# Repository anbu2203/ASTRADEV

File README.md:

## AstraDev
- AstraDev is a custom-designed development board created for embedded systems learning, prototyping, and real-world hardware design experience. The project follows a complete professional workflow—from schematic design to PCB layout, 3D verification, and manufacturing preparation.

# Project Overview
- AstraDev was designed to demonstrate a full PCB development lifecycle using industry-standard practices. The board design emphasizes clean schematics, organized PCB routing, proper grounding, and manufacturing readiness. All files have been verified and prepared for fabrication and assembly through JLCPCB.

# Schematic Design
- The schematic was designed using KiCad Schematic Editor
- All functional blocks were clearly separated:
Power supply and regulation
Microcontroller and clock circuitry
USB interface
Programming/debug interface
GPIO and peripheral connections
CUSTOM DEVBOARD guide-recommended components such as decoupling capacitors, pull-up/down resistors, and protection elements were included
Net labels and reference designators were standardized for clarity
Electrical Rule Check (ERC) was performed to ensure there were no schematic errors
The schematic was finalized and locked before PCB layout
.png)
# PCB Layout and Wiring

- PCB layout was completed using KiCad PCB Editor
- A 2-layer PCB was used:
Top layer (F.Cu) for signal routing
Bottom layer (B.Cu) primarily for ground plane and routing
Components were placed using functional grouping to reduce track length and noise
Power tracks were routed first, followed by critical signals and GPIO lines
Track widths were selected based on signal type:
GPIO and signal lines: minimum safe width
Power lines: wider tracks
A GND copper pour was added on both layers for proper grounding
Thermal reliefs and clearances were adjusted to ensure good solderability
Via stitching was used where necessary to improve ground connectivity
Design Rule Check (DRC) was run and all errors were resolved before production
.png)

# 3D Viewer Verification

- KiCad’s 3D Viewer was used to visually inspect the PCB
Component orientation, alignment, and placement were verified
Mechanical fit of connectors (USB, headers) was checked
Potential assembly issues were identified early
This step ensured the PCB would be physically correct before manufacturing

-  Manufacturing File Preparation:
Gerber and drill files were generated from KiCad
files were verified using Gerber viewer tools
A Bill of Materials (BOM) was generated and modified to meet JLCPCB requirements
A Component Placement List (CPL / Pick-and-Place) file was generated from the PCB editor
BOM and CPL headers were renamed to match JLCPCB’s accepted format
Only top-side assembly files were included
All production files were organized into a single production folder and compressed into a ZIP archive
.png)
.png)

# JLCPCB Checking and PCBA Preparation

- The production ZIP was uploaded to JLCPCB
PCB Assembly (PCBA) option was enabled
ENIG surface finish was selected for reliable soldering and flat pads
BOM components were reviewed:
Missing or incorrect parts were manually reassigned
Basic parts were prioritized to reduce cost
Pin headers and non-essential components were excluded from assembly
Component orientation and placement were verified using JLCPCB’s online PCBA viewer
Final checks were completed before submission
.png)

# Production Status

- Schematic completed and verified

- PCB layout completed and DRC cleared

- 3D verification completed

- BOM and CPL prepared and validated

- Ready for JLCPCB fabrication and assembly

- Awaiting funding for order placement

# Designed and documented by ANBU

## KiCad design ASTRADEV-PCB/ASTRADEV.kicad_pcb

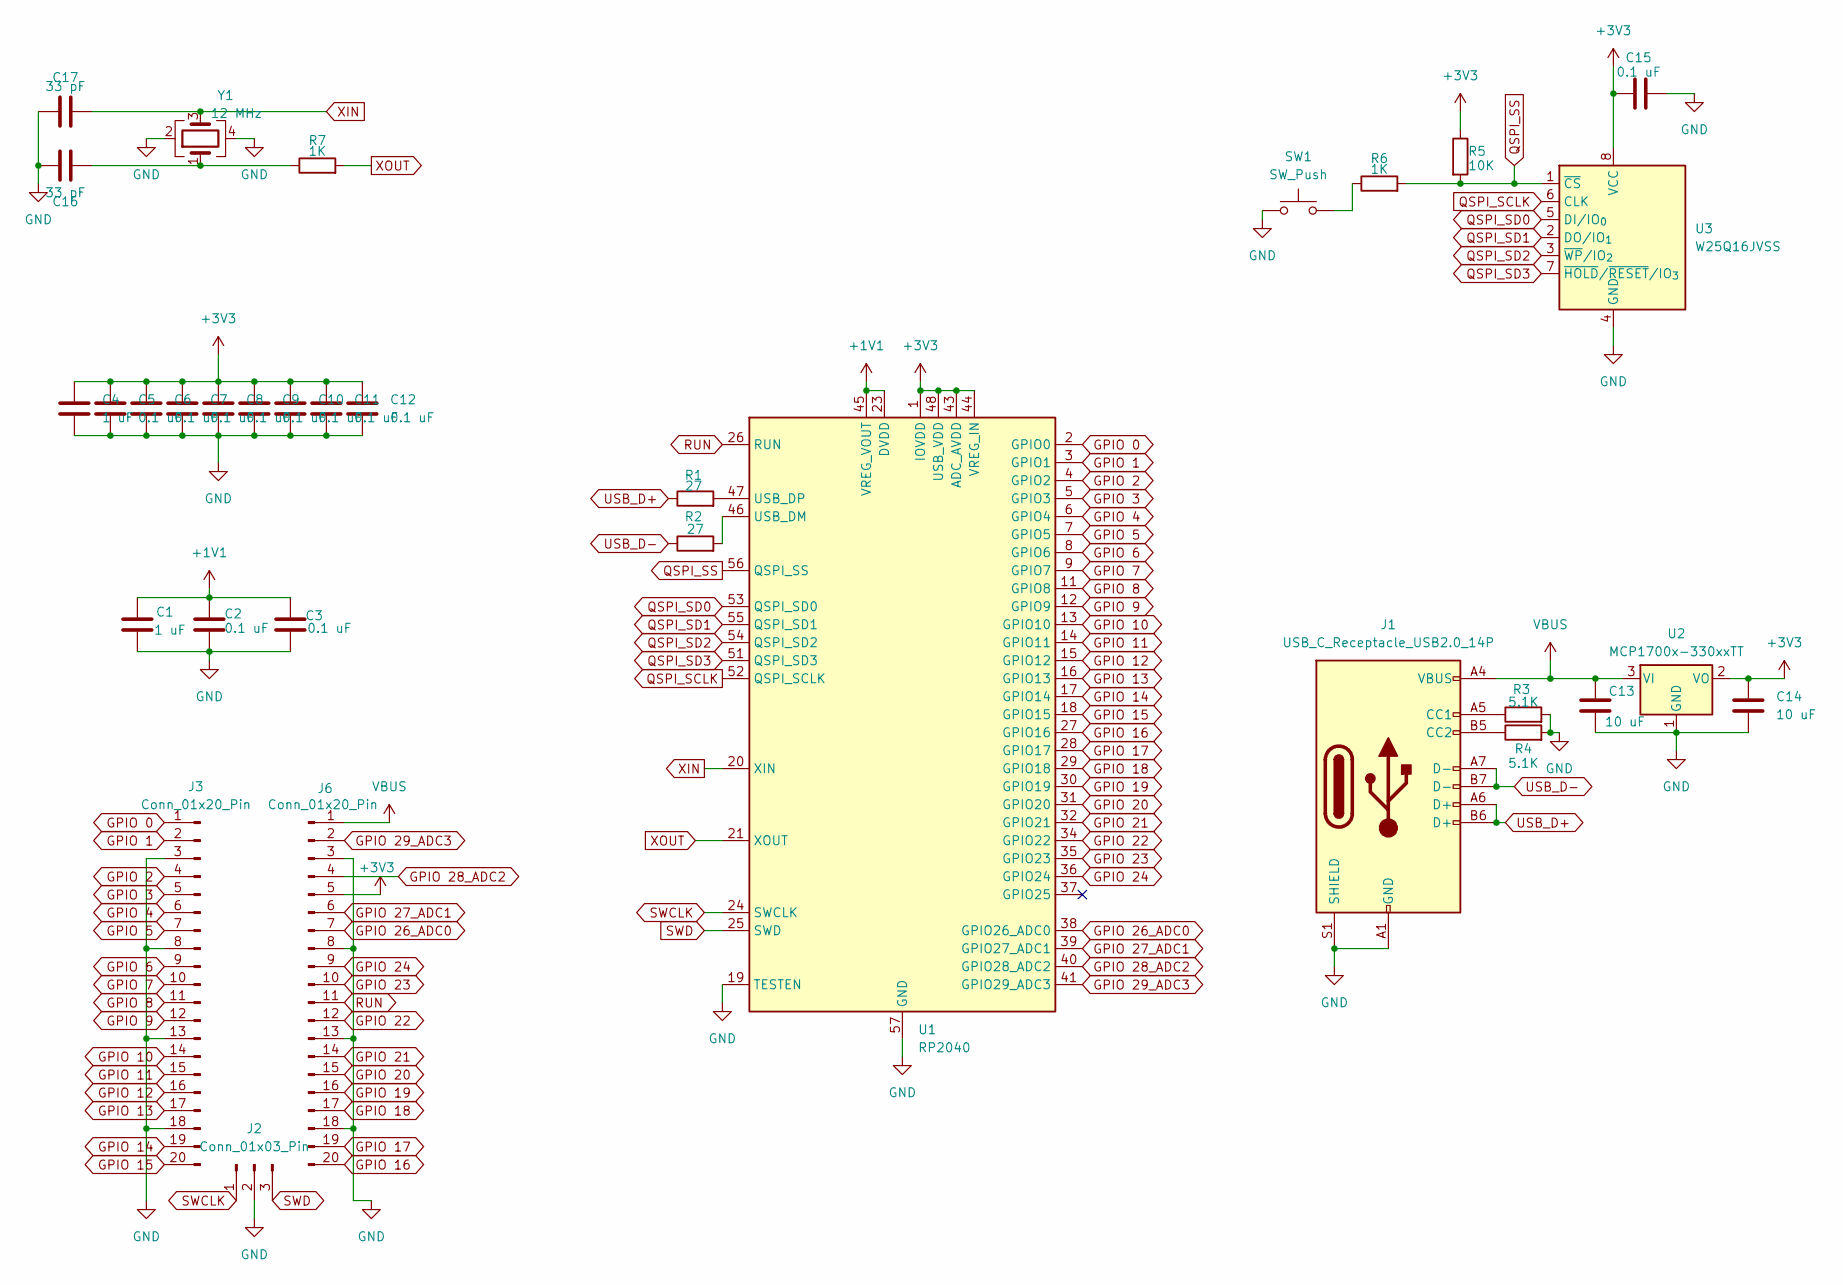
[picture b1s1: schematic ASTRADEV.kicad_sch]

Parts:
C1, C4: 1 uF; C_0402_1005Metric
C2, C3, C5, C6, C7, C8, C9, C10, C11, C12, C15: 0.1 uF; C_0402_1005Metric
C13, C14: 10 uF; C_0603_1608Metric
C16, C17: 33 pF; C_0402_1005Metric
J1: USB_C_Receptacle_USB2.0_14P; USB_C_Receptacle_HRO_TYPE-C-31-M-12
J2: Conn_01x03_Pin; PinHeader_1x03_P2.54mm_Vertical
J3, J6: Conn_01x20_Pin; PinHeader_1x20_P2.54mm_Vertical
R1, R2: 27; R_0402_1005Metric
R3, R4: 5.1K; R_0402_1005Metric
R5: 10K; R_0402_1005Metric
R6, R7: 1K; R_0402_1005Metric
SW1: SW_Push; SW_Push_SPST_NO_Alps_SKRK
U1: RP2040; QFN-56-1EP_7x7mm_P0.4mm_EP3.2x3.2mm
U2: MCP1700x-330xxTT; SOT-23
U3: W25Q16JVSS; Winbond_USON-8-1EP_3x2mm_P0.5mm_EP0.2x1.6mm
Y1: 12 MHz; Crystal_SMD_3225-4Pin_3.2x2.5mm

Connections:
+1V1: C1.1, C2.1, C3.1, U1.23 (DVDD), U1.45 (VREG_VOUT), U1.50 (DVDD)
+3V3: C4.1, C5.1, C6.1, C7.1, C8.1, C9.1, C10.1, C11.1, C12.1, C14.1, C15.1, J6.5, R5.1, U1.1 (IOVDD), U1.10 (IOVDD), U1.22 (IOVDD), U1.33 (IOVDD), U1.42 (IOVDD), U1.43 (ADC_AVDD), U1.44 (VREG_IN), U1.48 (USB_VDD), U1.49 (IOVDD), U2.2 (VO), U3.8 (VCC)
GND: C1.2, C2.2, C3.2, C4.2, C5.2, C6.2, C7.2, C8.2, C9.2, C10.2, C11.2, C12.2, C13.2, C14.2, C15.2, C16.1, C17.1, J1.A1 (GND), J1.A12 (GND), J1.B1 (GND), J1.B12 (GND), J1.S1 (SHIELD), J2.2, J3.3, J3.8, J3.13, J3.18, J6.3, J6.8, J6.13, J6.18, R3.2, R4.2, SW1.1, U1.19 (TESTEN), U1.57 (GND), U2.1 (GND), U3.4 (GND), Y1.2, Y1.4
GPIO 0: J3.1, U1.2 (GPIO0)
GPIO 1: J3.2, U1.3 (GPIO1)
GPIO 2: J3.4, U1.4 (GPIO2)
GPIO 3: J3.5, U1.5 (GPIO3)
GPIO 4: J3.6, U1.6 (GPIO4)
GPIO 5: J3.7, U1.7 (GPIO5)
GPIO 6: J3.9, U1.8 (GPIO6)
GPIO 7: J3.10, U1.9 (GPIO7)
GPIO 8: J3.11, U1.11 (GPIO8)
GPIO 9: J3.12, U1.12 (GPIO9)
GPIO 10: J3.14, U1.13 (GPIO10)
GPIO 11: J3.15, U1.14 (GPIO11)
GPIO 12: J3.16, U1.15 (GPIO12)
GPIO 13: J3.17, U1.16 (GPIO13)
GPIO 14: J3.19, U1.17 (GPIO14)
GPIO 15: J3.20, U1.18 (GPIO15)
GPIO 16: J6.20, U1.27 (GPIO16)
GPIO 17: J6.19, U1.28 (GPIO17)
GPIO 18: J6.17, U1.29 (GPIO18)
GPIO 19: J6.16, U1.30 (GPIO19)
GPIO 20: J6.15, U1.31 (GPIO20)
GPIO 21: J6.14, U1.32 (GPIO21)
GPIO 22: J6.12, U1.34 (GPIO22)
GPIO 23: J6.10, U1.35 (GPIO23)
GPIO 24: J6.9, U1.36 (GPIO24)
GPIO 26_ADC0: J6.7, U1.38 (GPIO26_ADC0)
GPIO 27_ADC1: J6.6, U1.39 (GPIO27_ADC1)
GPIO 28_ADC2: J6.4, U1.40 (GPIO28_ADC2)
GPIO 29_ADC3: J6.2, U1.41 (GPIO29_ADC3)
unnamed: C16.2, R7.1, Y1.1
unnamed: J1.A5 (CC1), R3.1
unnamed: J1.B5 (CC2), R4.1
unnamed: R6.1, SW1.2
unnamed: R2.2, U1.46 (USB_DM)
unnamed: R1.2, U1.47 (USB_DP)
QSPI_SCLK: U1.52 (QSPI_SCLK), U3.6 (CLK)
QSPI_SD0: U1.53 (QSPI_SD0), U3.5 (DI/IO_{0})
QSPI_SD1: U1.55 (QSPI_SD1), U3.2 (DO/IO_{1})
QSPI_SD2: U1.54 (QSPI_SD2), U3.3 (~WP/IO_{2})
QSPI_SD3: U1.51 (QSPI_SD3), U3.7 (~HOLD/~RESET/IO_{3})
QSPI_SS: R5.2, R6.2, U1.56 (QSPI_SS), U3.1 (~CS)
RUN: J6.11, U1.26 (RUN)
SWCLK: J2.1, U1.24 (SWCLK)
SWD: J2.3, U1.25 (SWD)
USB_D+: J1.A6 (D+), J1.B6 (D+), R1.1
USB_D-: J1.A7 (D-), J1.B7 (D-), R2.1
VBUS: C13.1, J1.A4 (VBUS), J1.A9 (VBUS), J1.B4 (VBUS), J1.B9 (VBUS), J6.1, U2.3 (VI)
XIN: C17.2, U1.20 (XIN), Y1.3
XOUT: R7.2, U1.21 (XOUT)

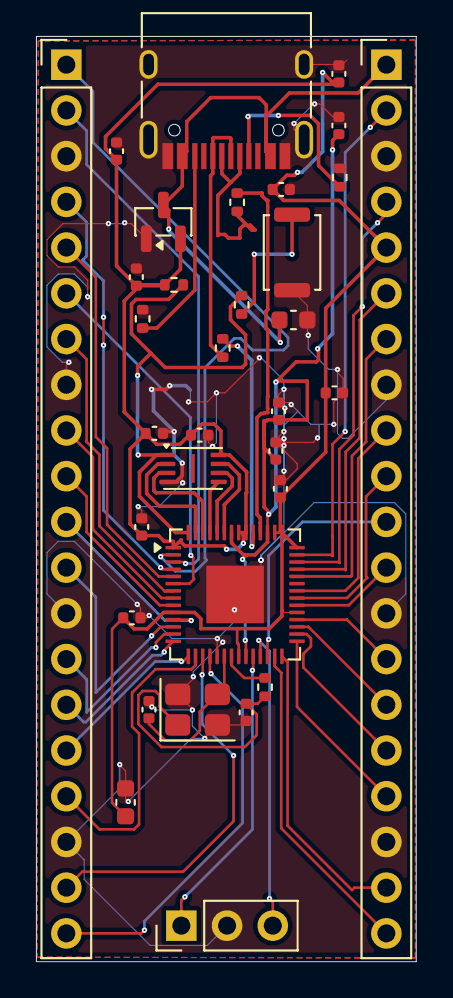
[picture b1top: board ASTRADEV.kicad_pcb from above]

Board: 2 copper layers, 21.1 x 51.4 mm, 33 parts (0 on the bottom side), 52 nets.
